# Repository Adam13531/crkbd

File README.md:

# Corne keyboard

The Corne keyboard is a split keyboard with 3x6 column staggered keys and 3 thumb keys,
based on [Helix](https://github.com/MakotoKurauchi/helix).
Crkbd stands for Corne Keyboard.

## Adam's updates

I wanted a very specific setup: a v3, 5-column choc keyboard. I forked this repo from https://github.com/daysgobye/crkbd/tree/choc-v3, so I got two of those things for free. I then modified the design to chop a column of keys off from both sides. I ordered the PCBs from [JLCPCB](https://jlcpcb.com/) using these settings (which will get you _five_ keyboards' worth of parts, not 2½):

The resulting PCB looks like this:

I derived a bill of materials based on [this reddit post](https://www.reddit.com/r/crkbd/comments/esv3i8/guide_corne_diy_kit/), [this GitHub page](https://github.com/ItsWaffIe/waffle_corne/wiki/Build-Log#parts), and [this great build guide](https://medwa.io/docs/corne-lp-build-guide/#bom). For a frame of reference, I ordered everything from AliExpress in October, 2021.

**Part**|**Quantity ordered**|**Cost (USD)**
:-----:|:-----:|:-----:
[Kailh 1.5u low-profile choc keycaps](https://www.aliexpress.com/item/33024722080.html)|30|$8.50
[Kailh 1u low-profile choc keycaps](https://www.aliexpress.com/item/33026798318.html)|60|$16.40
[Kailh low-profile choc red crystal](https://www.aliexpress.com/item/4001016150022.html)|70|$51.30
[Low-profile Kailh sockets](https://www.aliexpress.com/item/1005002695808124.html)|44|$4.40
[40-pin connector header pins](https://www.aliexpress.com/item/4001345538843.html)|5|$1.55
[40-pin connector header sockets](https://www.aliexpress.com/item/32847384633.html)|10|$1.80
[TRRS jack](https://www.aliexpress.com/item/33029465106.html)|10|$0.75
[Diodes](https://www.aliexpress.com/item/4000685043735.html)|100|$0.69
[Pro Micro microcontroller](https://www.aliexpress.com/item/32888212119.html)|2|$10.14
[Per-key LED](https://www.aliexpress.com/item/4000475685852.html)|100|$9.12
[Underglow LED](https://www.aliexpress.com/item/32830413032.html)|100|$10.58
Shipping to US|1|~$20
Tax|1|~$14

Full part names in case the links eventually die:

- Kailh 1.5u Low Profile Keycaps 1350 chocolate switch special cream white for gaming DIY mechanical keyboard ABS material 30PCS
- Kailh 1.0u Low Profile Keycaps 1350 chocolate switch special cream white for gaming DIY mechanical keyboard ABS material 30PCS
- Kailh Choc Red Crystal Switch low profile Switch Chocolate Mechanical Keyboard Switch RGB SMD white stem linear hand feeling
- Mechanical Keyboard Low Profile Switches Kailh PCB Socket CPG135001S30
- 5pcs 40 Pin Connector Header Round Needle 1x40 Golden Pin Single Row Male 2.54mm Breakable Pin Connector Strip
- 10pcs 1X40PIN 2.54MM 1x40 Pin 2.54 Round Female Pin Header Connector
- 10 Pcs TRRS 3.5 MM Audio Jack Connector Through Holes PCB Horizontal 4 Contact 4 Conductor Right Angle No Internal Switch 4 Pole
- 100pcs/lot 1206 1N4148W T4 1N4148 IN4148 SOD-123 IC
- Mini/Type-C/Micro USB Pro Micro ATMEGA32U4 5V/16MHZ module With the bootloader for arduino with 2 row pin header for arduino. Product properties: TYPE-C USB 3-6V
- 50-2000PCS SK6812 MINI-E RGB (similar with WS2812B) SK6812 3228 SMD Pixels LED Chip Individually Addressable Full Color DC 5V. Product properties: 100 PCS
- 50-1000pcs SK6812 WS2812B IC Bulit in 5050 3535 RGB SMD Addressable Digital RGB Full Color LED Chip Pixels Light Bead DC5V. Product properties: 5050 + White chip + 100pcs

### Adam's notes

- **Miscellaneous**
    - I had basically no idea what I was doing for most of this. (◕‿◕✿)
    - Do not attach/detach the TRRS cable while the keyboard is powered on ([reference](https://docs.qmk.fm/#/feature_split_keyboard?id=considerations)).
    - For testing LEDs, use the `soundmonster` keymap, which has all lights on by default. The underglow LEDs all need to be connected for the per-key lighting to work. If _nothing_ turns on, then it means you should look at the underglow LEDs or your firmware. If _some_ turn on, then you should look near the last LED to light up (or the next LED to _not_ light up).
    - I made [a video](https://www.youtube.com/watch?v=uilLCe1fvb0) talking about my keyboard journey. Skip to the end if you want to see the build that this design produced.
- **BOM notes**
    - The BOM doesn't contain:
        - OLEDs (because I didn't want them)
        - Physical reset buttons (I opt to use the `RESET` key that I've mapped through QMK)
        - A TRRS cable (I already had one)
- **Design changes I'd make if I weren't lazy**
    - I never touched the schematic file, just the PCB, so the schematic may be totally wrong. This doesn't impact anything in the manufacturing process, but I believe it affects the BOM that you can have KiCad generate.
    - Delete the `JLCJLCJLCJLC` text on the PCB. It turns out it didn't get overwritten with the order number, so now the `JLCJLCJLCJLC` text is visible on the underside of the keyboard. The order number got printed on the cutaway part.
    - I mislabeled the LEDs in the silkscreen (some numbers are out of order—definitely at least `24 25 26`). The LED numbers also may not correspond to the LEDs in QMK, but that may be for a different reason.

## Lineup

- corne-classic([JP](corne-classic/doc/buildguide_jp.md)/[EN](corne-classic/doc/buildguide_en.md)):
    Corne for Cherry MX switches
- corne-cherry([JP](corne-cherry/doc/buildguide_jp.md)) ([tilting, JP](corne-cherry/doc/v2/buildguide_tilting_tenting_plate_jp.md)):
    Hotswappable Corne for Cherry MX switches by kailh PCB sockets.
- corne-chocolate([JP](corne-chocolate/doc/buildguide_jp.md)/[EN](corne-chocolate/doc/buildguide_en.md)):
    Hotswappable Corne for Chocolate switches using Kailh PCB hot-swap sockets.
- corne-light([JP](corne-light/doc/buildguide_jp.md)):
    Light-weight Corne (Easy build with a simple PCB).

## Photos

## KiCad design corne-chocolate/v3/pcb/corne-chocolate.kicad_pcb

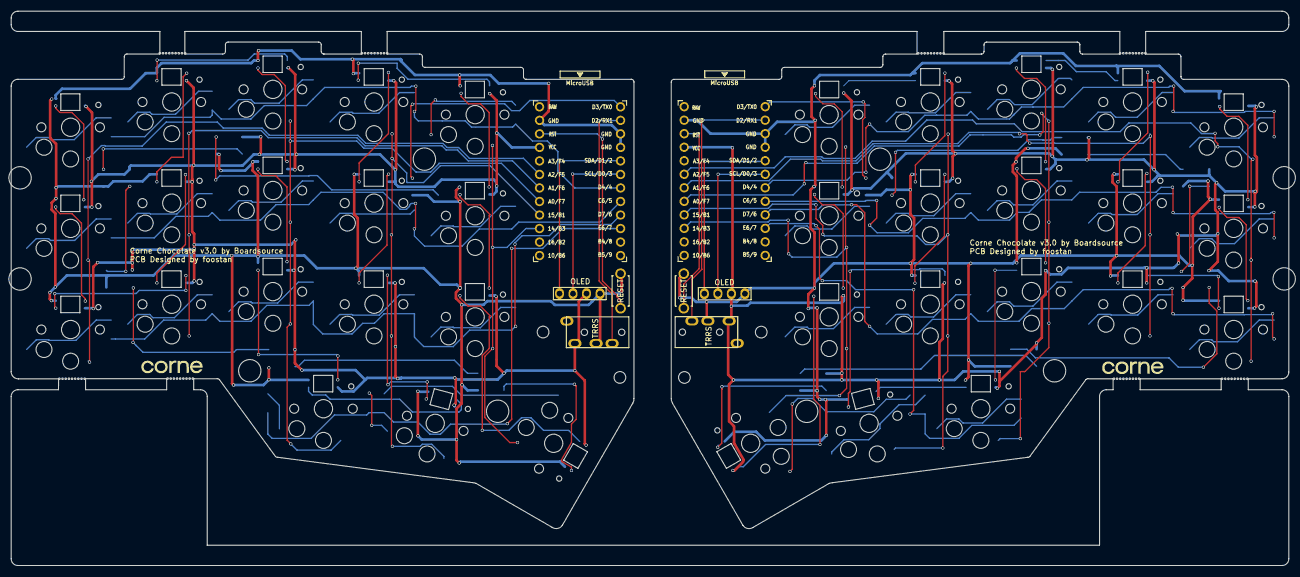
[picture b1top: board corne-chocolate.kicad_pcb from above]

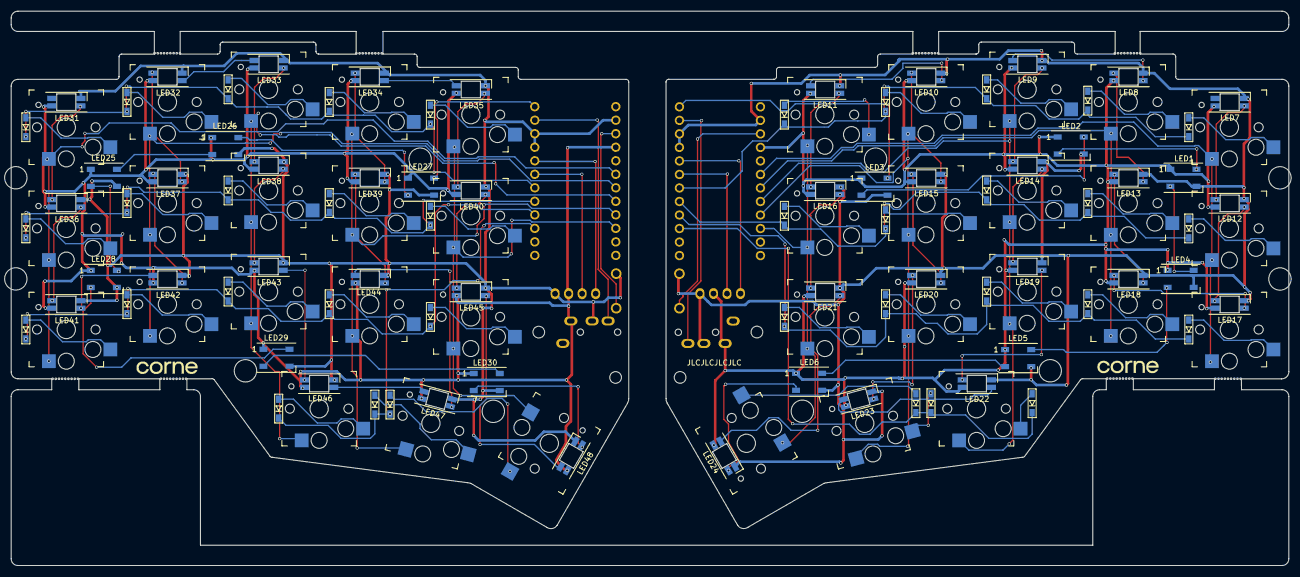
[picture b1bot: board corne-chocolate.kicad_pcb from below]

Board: 2 copper layers, 240.0 x 104.1 mm, 142 parts (91 on the bottom side), 114 nets.

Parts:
D2, D3, D4, D5, D6, D8, D9, D10, D11, D12, D14, D15, D16, D17, D18, D19, D20, D21, D23, D24, D25, D26, D27, D29, D30, D31, D32, D33, D35, D36, D37, D38, D39, D40, D41, D42: D; D3_SMD_v2
J1, J3: MJ-4PP-9; MJ-4PP-9_1side
J2, J4: OLED; OLED_1side
LED1, LED2, LED3, LED4, LED5, LED6, LED25, LED26, LED27, LED28, LED29, LED30: WS2812B; LED_WS2812B_PLCC4_5.0x5.0mm_P3.2mm
LED7, LED8, LED9, LED10, LED11, LED12, LED13, LED14, LED15, LED16, LED17, LED18, LED19, LED20, LED21, LED22, LED23, LED24, LED31, LED32, LED33, LED34, LED35, LED36, LED37, LED38, LED39, LED40, LED41, LED42, LED43, LED44, LED45, LED46, LED47, LED48: YS-SK6812MINI-E
RSW1, RSW2: SW_PUSH; ResetSW_1side
Ref**: Val**; M2_HOLE_v2
Ref**#2, Ref**#3, Ref**#4, Ref**#5, Ref**#6, Ref**#7, Ref**#8, Ref**#9, Ref**#10, Ref**#11, Ref**#12, Ref**#13, Ref**#14: Val**; M2_HOLE_v2
SW1, SW2, SW3, SW4, SW5, SW6, SW7, SW8, SW9, SW10, SW11, SW12, SW13, SW14, SW15, SW16, SW17, SW18, SW19, SW20, SW21, SW22, SW23, SW24, SW25, SW26, SW27, SW28, SW29, SW30, SW31, SW32, SW33, SW34, SW35, SW36: SW_PUSH; PG1350_socket_clean
U1, U2: ProMicro; ProMicro_v3

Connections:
GND: J1.C, J2.4, LED1.3, LED2.3, LED3.3, LED4.3, LED5.3, LED6.3, LED7.3, LED8.3, LED9.3, LED10.3, LED11.3, LED12.3, LED13.3, LED14.3, LED15.3, LED16.3, LED17.3, LED18.3, LED19.3, LED20.3, LED21.3, LED22.3, LED23.3, LED24.3, RSW1.2, U1.3, U1.4, U1.23
GNDA: J3.C, J4.1, LED25.3, LED26.3, LED27.3, LED28.3, LED29.3, LED30.3, LED31.3, LED32.3, LED33.3, LED34.3, LED35.3, LED36.3, LED37.3, LED38.3, LED39.3, LED40.3, LED41.3, LED42.3, LED43.3, LED44.3, LED45.3, LED46.3, LED47.3, LED48.3, RSW2.2, U2.3, U2.4, U2.23
LED: LED3.4, U1.1
LED_r: LED27.4, U2.1
unnamed: D2.2, SW1.2
unnamed: D3.2, SW2.2
unnamed: D4.2, SW3.2
unnamed: D5.2, SW4.2
unnamed: D6.2, SW5.2
unnamed: D8.2, SW6.2
unnamed: D9.2, SW7.2
unnamed: D10.2, SW8.2
unnamed: D11.2, SW9.2
unnamed: D12.2, SW10.2
unnamed: D14.2, SW11.2
unnamed: D15.2, SW12.2
unnamed: D16.2, SW13.2
unnamed: D17.2, SW14.2
unnamed: D18.2, SW15.2
unnamed: D19.2, SW16.2
unnamed: D20.2, SW17.2
unnamed: D21.2, SW18.2
unnamed: D23.2, SW19.2
unnamed: D24.2, SW20.2
unnamed: D25.2, SW21.2
unnamed: D26.2, SW22.2
unnamed: D27.2, SW23.2
unnamed: D29.2, SW24.2
unnamed: D30.2, SW25.2
unnamed: D31.2, SW26.2
unnamed: D32.2, SW27.2
unnamed: D33.2, SW28.2
unnamed: D35.2, SW29.2
unnamed: D36.2, SW30.2
unnamed: D37.2, SW31.2
unnamed: D38.2, SW32.2
unnamed: D39.2, SW33.2
unnamed: D40.2, SW34.2
unnamed: D41.2, SW35.2
unnamed: D42.2, SW36.2
unnamed: LED1.2, LED4.4
unnamed: LED1.4, LED2.2
unnamed: LED2.4, LED3.2
unnamed: LED4.2, LED5.4
unnamed: LED5.2, LED6.4
unnamed: LED8.4, LED9.2
unnamed: LED9.4, LED14.2
unnamed: LED10.2, LED15.4
unnamed: LED10.4, LED11.2
unnamed: LED11.4, LED16.2
unnamed: LED7.4, LED12.2
unnamed: LED12.4, LED17.2
unnamed: LED13.2, LED18.4
unnamed: LED8.2, LED13.4
unnamed: LED14.4, LED19.2
unnamed: LED15.2, LED20.4
unnamed: LED16.4, LED21.2
unnamed: LED17.4, LED18.2
unnamed: LED19.4, LED22.2
unnamed: LED20.2, LED23.4
unnamed: LED21.4, LED24.2
unnamed: LED22.4, LED23.2
unnamed: LED6.2, LED24.4
unnamed: LED25.2, LED28.4
unnamed: LED25.4, LED26.2
unnamed: LED26.4, LED27.2
unnamed: LED28.2, LED29.4
unnamed: LED29.2, LED30.4
unnamed: LED30.2, LED48.4
unnamed: LED31.4, LED36.2
unnamed: LED32.2, LED37.4
unnamed: LED32.4, LED33.2
unnamed: LED33.4, LED38.2
unnamed: LED34.2, LED39.4
unnamed: LED34.4, LED35.2
unnamed: LED35.4, LED40.2
unnamed: LED36.4, LED41.2
unnamed: LED37.2, LED42.4
unnamed: LED38.4, LED43.2
unnamed: LED39.2, LED44.4
unnamed: LED40.4, LED45.2
unnamed: LED41.4, LED42.2
unnamed: LED43.4, LED46.2
unnamed: LED44.2, LED47.4
unnamed: LED45.4, LED48.2
unnamed: LED46.4, LED47.2
SCL: J2.2, U1.6
SCL_r: J4.3, U2.6
SDA: J2.1, U1.5
SDA_r: J4.4, U2.5
VCC: J1.D, J2.3, LED1.1, LED2.1, LED3.1, LED4.1, LED5.1, LED6.1, LED7.1, LED8.1, LED9.1, LED10.1, LED11.1, LED12.1, LED13.1, LED14.1, LED15.1, LED16.1, LED17.1, LED18.1, LED19.1, LED20.1, LED21.1, LED22.1, LED23.1, LED24.1, U1.21
VDD: J3.D, J4.2, LED25.1, LED26.1, LED27.1, LED28.1, LED29.1, LED30.1, LED31.1, LED32.1, LED33.1, LED34.1, LED35.1, LED36.1, LED37.1, LED38.1, LED39.1, LED40.1, LED41.1, LED42.1, LED43.1, LED44.1, LED45.1, LED46.1, LED47.1, LED48.1, U2.21
col1: SW1.1, SW6.1, SW11.1, U1.19
col1_r: SW19.1, SW24.1, SW29.1, U2.19
col2: SW2.1, SW7.1, SW12.1, U1.18
col2_r: SW20.1, SW25.1, SW30.1, U2.18
col3: SW3.1, SW8.1, SW13.1, SW16.1, U1.17
col3_r: SW21.1, SW26.1, SW31.1, SW34.1, U2.17
col4: SW4.1, SW9.1, SW14.1, SW17.1, U1.16
col4_r: SW22.1, SW27.1, SW32.1, SW35.1, U2.16
col5: SW5.1, SW10.1, SW15.1, SW18.1, U1.15
col5_r: SW23.1, SW28.1, SW33.1, SW36.1, U2.15
data: J1.B, U1.2
data_r: J3.B, U2.2
reset: RSW1.1, U1.22
reset_r: RSW2.1, U2.22
row0: D2.1, D3.1, D4.1, D5.1, D6.1, U1.7
row0_r: D23.1, D24.1, D25.1, D26.1, D27.1, U2.7
row1: D8.1, D9.1, D10.1, D11.1, D12.1, U1.8
row1_r: D29.1, D30.1, D31.1, D32.1, D33.1, U2.8
row2: D14.1, D15.1, D16.1, D17.1, D18.1, U1.9
row2_r: D35.1, D36.1, D37.1, D38.1, D39.1, U2.9
row3: D19.1, D20.1, D21.1, U1.10
row3_r: D40.1, D41.1, D42.1, U2.10

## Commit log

2021-10-17 Add WIP 5-column PCB
2021-10-17 Fix incorrect connections
2021-10-17 Fix boundaries and add "JLCJLCJLCJLC"
2021-10-18 Clean up PCB
    - Relabeled LEDs and switch numbers
    - Added dimensions back in
    - Updated the title/comments
2021-10-21 Round all corners and delete extra trace
2021-10-26 Update README.md
    - Clarify changes
    - Add BOM
2022-04-05 Remove note about cheap microcontrollers
    The memory amount is pretty standard and fine.
2022-07-10 Fix swapped links
    (thanks for pointing this out, Rhymu!)
2024-11-26 Fix broken build-guide link
